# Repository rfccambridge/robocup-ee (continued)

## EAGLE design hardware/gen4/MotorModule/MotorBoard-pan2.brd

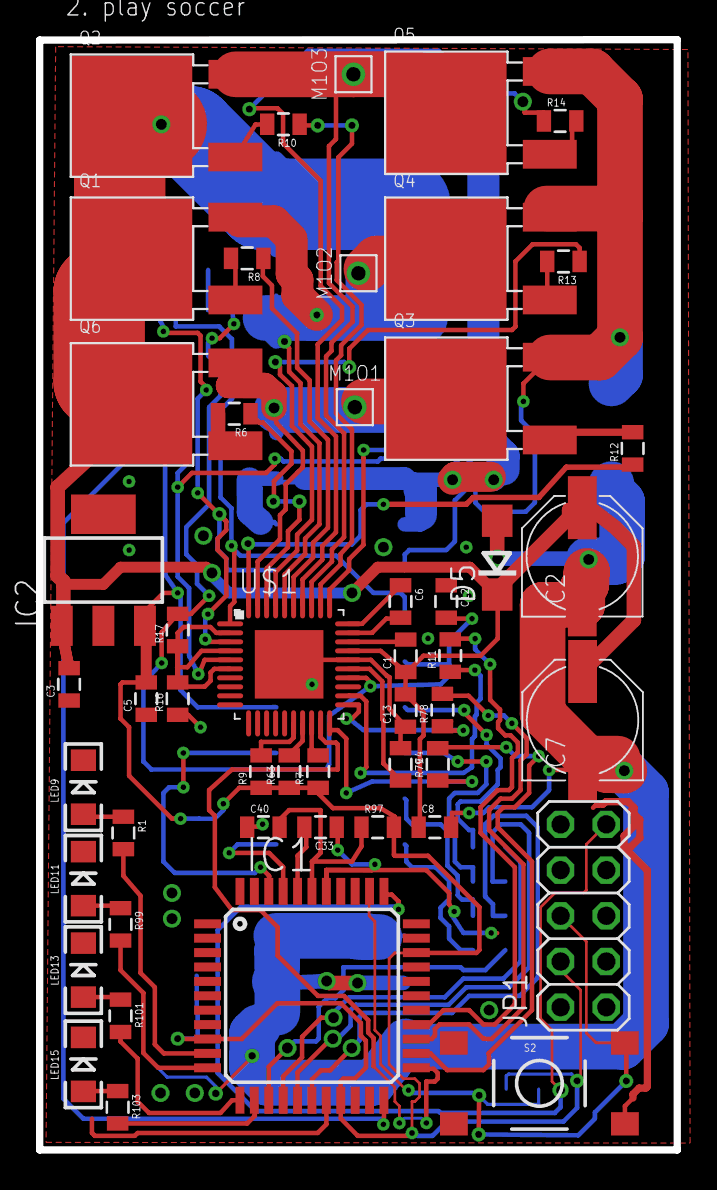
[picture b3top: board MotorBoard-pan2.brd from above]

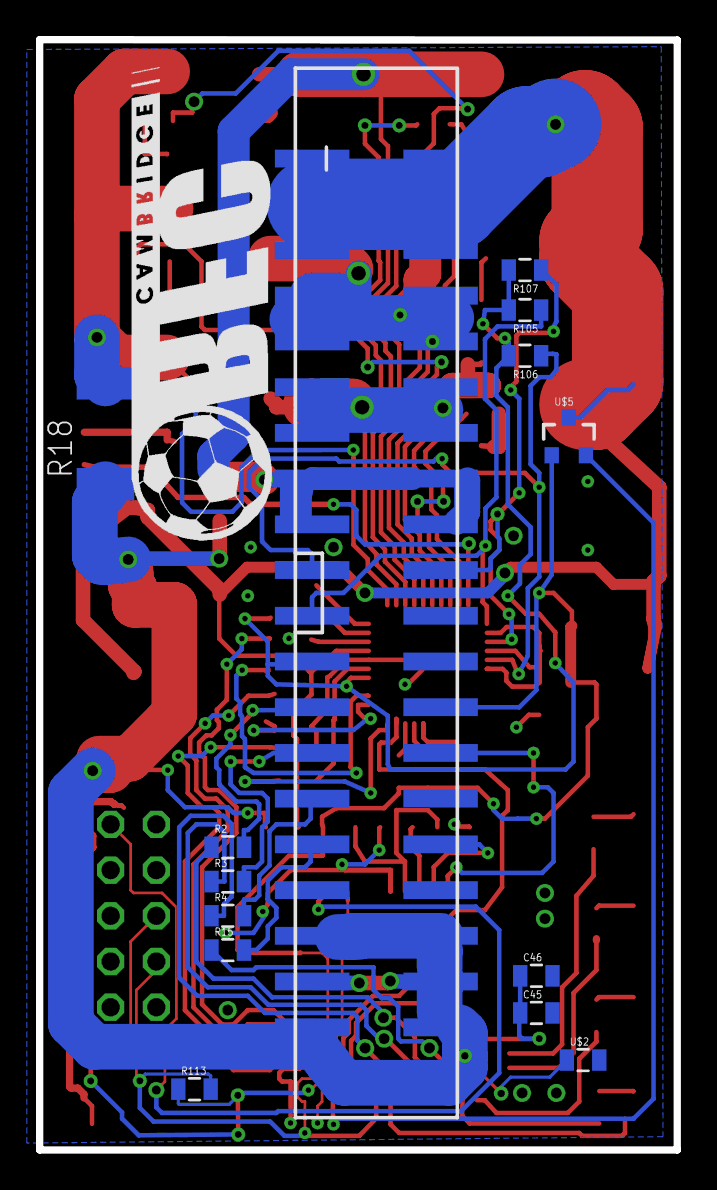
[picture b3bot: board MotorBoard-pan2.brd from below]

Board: 2 copper layers, 35.4 x 61.7 mm, 66 parts (14 on the bottom side), 62 nets.

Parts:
C1, C4, C45: 1uF; 0805
C2, C7: 100uF; PANASONIC_D
C3, C5, C8, C12, C33, C40: .1uF; 0805
C6, C13: 0.1uF; 0805
C46: .01uF; 0805
D5: DIODE-ZENERDO214AC; DO214AC
FRAME7: FRAME-LETTER; CREATIVE_COMMONS
GEN_4_REV_A: Fall 2015; LOGO
IC1: XMEGA16A4A; TQFP44
IC2: 3.3V REG; SOT223
JP1: DEBUG; 2X05
JP3: M20X2SHROUDED_SMT; 2X20_SHROUDED_SMT
LED9, LED11, LED13, LED15: LED-1206
M1O1, M1O2, M1O3: TEST_PT; TESTING_PT
Q1, Q2, Q3, Q4, Q5, Q6: DPAK
R1, R11, R78, R79, R99, R101, R103: 1k; 0805
R2, R3, R4, R15: 4.7k; 0805
R6, R8, R10, R12, R13, R14: 240; 0805
R7, R63: 30k; 0805
R9: 15k; 0805
R16, R17: 2K; 0805
R18: 0.05; R2512
R97, R105, R106, R107, R113: 10k; 0805
S2: TAC_SWITCHSMD; TACTILE-SWITCH-SMD
U$1: DRV8307; QFN40-6X6
U$2: INDUCTOR; 0805
U$5: MCP9700SMD; SOT23-3

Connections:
3.3V: C5.2, C45.1, C46.1, IC1.9, IC1.19, IC1.31, IC2.3, JP1.4, JP3.26, R7.1, R9.1, R63.1, R97.2, R113.2, U$5.1
5V: C12.2, JP3.23, R17.2, R105.2, R106.2, R107.2, U$1.24
12V: C1.1, C2.+, C3.2, C7.+, C8.1, C13.2, D5.C, IC2.1, JP3.1, JP3.2, JP3.3, JP3.4, JP3.5, JP3.6, Q1.DRAIN, Q2.DRAIN, Q6.DRAIN, U$1.27
12VGND: C2.-, C7.-, C8.2, D5.A, JP3.35, JP3.36, JP3.37, JP3.38, JP3.39, JP3.40, R18.1, U$2.1
AVCC: C40.2, IC1.39, R97.1
BREN: IC1.24, R79.2
DATA: IC1.34, JP1.9
DIR: IC1.25, R78.2
ENABLE: IC1.26, R11.2
GLED1: IC1.10, R1.2
GLED2: IC1.11, R99.2
GLED3: IC1.12, R101.2
GLED4: IC1.13, R103.2
GND: C3.1, C4.1, C5.1, C12.1, C13.1, C33.1, C40.1, C45.2, C46.2, IC1.8, IC1.18, IC1.30, IC1.38, IC2.2, IC2.4, JP1.10, JP3.22, JP3.30, JP3.33, JP3.34, LED9.C, LED11.C, LED13.C, LED15.C, R16.1, S2.4, U$1.26, U$1.P$3, U$2.2, U$5.3
M1H1: JP3.19, R106.1, U$1.5
M1H2: JP3.20, R107.1, U$1.3
M1H3: JP3.21, R105.1, U$1.1
M1O1: JP3.11, JP3.12, JP3.13, JP3.14, M1O1.P$1, Q3.DRAIN, Q6.SOURCE, U$1.39
M1O2: JP3.7, JP3.8, JP3.9, JP3.10, M1O2.P$1, Q1.SOURCE, Q4.DRAIN, U$1.36
M1O3: JP3.15, JP3.16, JP3.17, JP3.18, M1O3.P$1, Q2.SOURCE, Q5.DRAIN, U$1.33
M1QA: IC1.42, JP3.28
M1QB: IC1.41, JP3.32
MISO: IC1.16, R3.1
MOSI: IC1.15, R2.1
unnamed: LED9.A, R1.1
unnamed: C6.2, U$1.29
unnamed: JP3.27, R3.2
unnamed: JP3.29, R4.2
unnamed: Q6.GATE, R6.2
unnamed: Q1.GATE, R8.2
unnamed: C33.2, IC1.40
unnamed: C6.1, U$1.30
unnamed: Q2.GATE, R10.2
unnamed: Q3.GATE, R12.2
unnamed: C1.2, U$1.28
unnamed: Q4.GATE, R13.2
unnamed: Q5.GATE, R14.2
unnamed: C4.2, U$1.25
unnamed: R6.1, U$1.38
unnamed: R14.1, U$1.34
unnamed: R13.1, U$1.37
unnamed: R12.1, U$1.40
unnamed: R8.1, U$1.35
unnamed: R10.1, U$1.32
unnamed: R16.2, R17.1, U$1.2, U$1.4, U$1.6
unnamed: R79.1, U$1.20
unnamed: R7.2, U$1.18
unnamed: R63.2, U$1.17
unnamed: R9.2, U$1.16
unnamed: R11.1, U$1.22
unnamed: JP3.31, R15.2
unnamed: JP3.25, R2.2
unnamed: R78.1, U$1.21
unnamed: LED11.A, R99.1
unnamed: LED13.A, R101.1
unnamed: LED15.A, R103.1
O1: Q3.SOURCE, Q4.SOURCE, Q5.SOURCE, R18.2, U$1.31
PWM1: IC1.23, U$1.19
RESET: IC1.35, JP1.6, R113.1, S2.2
SCK: IC1.17, R4.1
SS_M: IC1.14, R15.1
TSENSE1: IC1.22, U$5.2

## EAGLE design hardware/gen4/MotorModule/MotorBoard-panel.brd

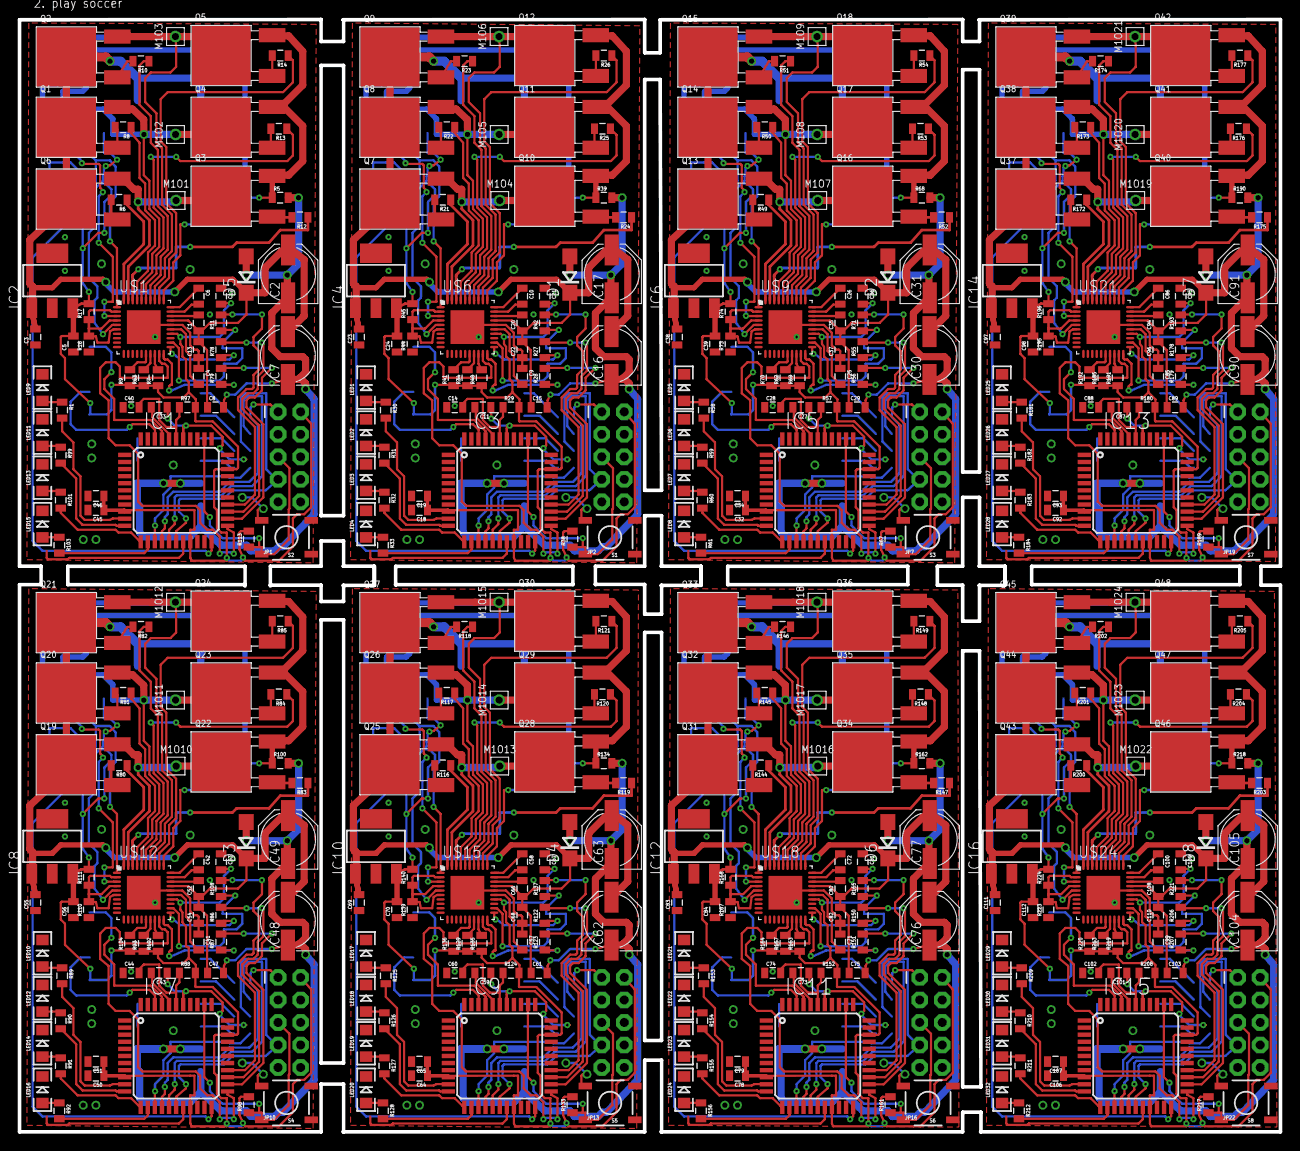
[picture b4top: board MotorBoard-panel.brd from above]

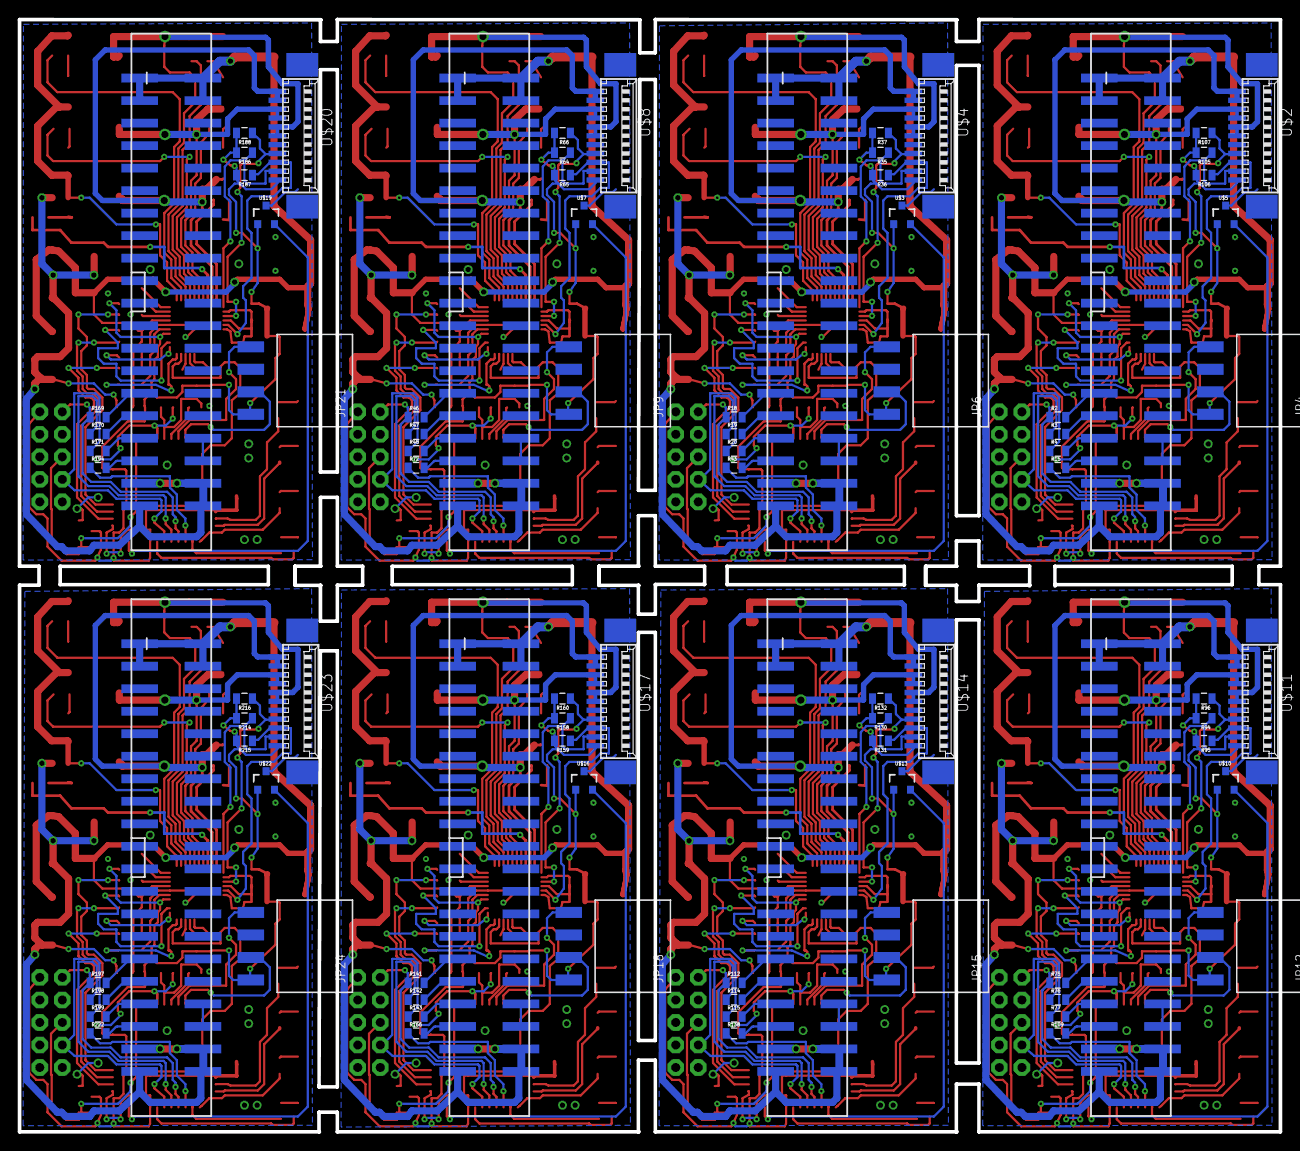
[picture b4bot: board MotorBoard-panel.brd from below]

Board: 2 copper layers, 142.3 x 125.5 mm, 522 parts (88 on the bottom side), 480 nets.

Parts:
C1, C4, C6, C9, C10, C18, C20, C25, C26, C32, C35, C41, C42, C45, C50, C52, C57, C58, C64, C66, C71, C72, C78, C80, C85, C86, C92, C94, C99, C100, C106, C108: 1uF; 0805
C2, C7, C16, C17, C30, C31, C48, C49, C62, C63, C76, C77, C90, C91, C104, C105: 100uF; PANASONIC_D
C3, C5, C8, C11, C12, C14, C15, C21, C23, C24, C27, C28, C29, C33, C36, C38, C39, C40, C43, C44, C47, C53, C55, C56, C59, C60, C61, C67, C69, C70, C73, C74, C75, C81, C83, C84, C87, C88, C89, C95, C97, C98, C101, C102, C103, C109, C111, C112: .1uF; 0805
C13, C22, C37, C54, C68, C82, C96, C110: 0.1uF; 0805
C19, C34, C46, C51, C65, C79, C93, C107: .01uF; 0805
D1, D2, D3, D4, D5, D6, D7, D8: DIODE-ZENERDO214AC; DO214AC
FRAME7: FRAME-LETTER; CREATIVE_COMMONS
GEN_4_REV_A: Fall 2015; LOGO
IC1, IC3, IC5, IC7, IC9, IC11, IC13, IC15: XMEGA16A4A; TQFP44
IC2, IC4, IC6, IC8, IC10, IC12, IC14, IC16: SOT223
JP1, JP2, JP7, JP10, JP13, JP16, JP19, JP22: 2X5-SHROUDED-NS
JP3, JP5, JP8, JP11, JP14, JP17, JP20, JP23: M20X2SHROUDED_SMT; 2X20_SHROUDED_SMT
JP4, JP6, JP9, JP12, JP15, JP18, JP21, JP24: 1X04_SMD_RA_FEMALE
LED1, LED2, LED3, LED4, LED5, LED6, LED7, LED8, LED9, LED10, LED11, LED12, LED13, LED14, LED15, LED16, LED17, LED18, LED19, LED20, LED21, LED22, LED23, LED24, LED25, LED26, LED27, LED28, LED29, LED30, LED31, LED32: LED-1206
M1O1, M1O2, M1O3, M1O4, M1O5, M1O6, M1O7, M1O8, M1O9, M1O10, M1O11, M1O12, M1O13, M1O14, M1O15, M1O16, M1O17, M1O18, M1O19, M1O20, M1O21, M1O22, M1O23, M1O24: TEST_PT; TESTING_PT
Q1, Q2, Q3, Q4, Q5, Q6, Q7, Q8, Q9, Q10, Q11, Q12, Q13, Q14, Q15, Q16, Q17, Q18, Q19, Q20, Q21, Q22, Q23, Q24, Q25, Q26, Q27, Q28, Q29, Q30, Q31, Q32, Q33, Q34, Q35, Q36, Q37, Q38, Q39, Q40, Q41, Q42, Q43, Q44, Q45, Q46, Q47, Q48: DPAK
R1, R11, R27, R28, R30, R31, R32, R33, R42, R55, R56, R58, R59, R60, R61, R71, R78, R79, R86, R87, R89, R90, R91, R92, R99, R101, R103, R108, R122, R123, R125, R126, R127, R128, R137, R150, R151, R153, R154, R155, R156, R165, R178, R179, R181, R182, R183, R184, R193, R206, R207, R209, R210, R211, R212, R221: 1k; 0805
R2, R3, R4, R15, R18, R19, R20, R43, R46, R47, R48, R72, R75, R76, R77, R109, R112, R114, R115, R138, R141, R142, R143, R166, R169, R170, R171, R194, R197, R198, R199, R222: 4.7k; 0805
R5, R39, R68, R100, R134, R162, R190, R218: 0.05; 0805
R6, R8, R10, R12, R13, R14, R21, R22, R23, R24, R25, R26, R49, R50, R51, R52, R53, R54, R80, R81, R82, R83, R84, R85, R116, R117, R118, R119, R120, R121, R144, R145, R146, R147, R148, R149, R172, R173, R174, R175, R176, R177, R200, R201, R202, R203, R204, R205: 240; 0805
R7, R34, R40, R62, R63, R69, R93, R102, R129, R135, R157, R163, R185, R191, R213, R219: 30k; 0805
R9, R41, R70, R104, R136, R164, R192, R220: 15k; 0805
R16, R17, R44, R45, R73, R74, R110, R111, R139, R140, R167, R168, R195, R196, R223, R224: 2K; 0805
R29, R35, R36, R37, R38, R57, R64, R65, R66, R67, R88, R94, R95, R96, R97, R98, R105, R106, R107, R113, R124, R130, R131, R132, R133, R152, R158, R159, R160, R161, R180, R186, R187, R188, R189, R208, R214, R215, R216, R217: 10k; 0805
S1, S2, S3, S4, S5, S6, S7, S8: TAC_SWITCHSMD; TACTILE-SWITCH-SMD
U$1, U$6, U$9, U$12, U$15, U$18, U$21, U$24: DRV8307; QFN40-6X6
U$2, U$4, U$8, U$11, U$14, U$17, U$20, U$23: MOTORCON; GEN3CON
U$3, U$5, U$7, U$10, U$13, U$16, U$19, U$22: MCP9700SMD; SOT23-3

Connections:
3.3V: C5.2, C12.2, C45.1, C46.1, IC1.9, IC1.19, IC1.31, IC2.3, JP1.2, JP4.1, R7.1, R9.1, R17.2, R63.1, R97.2, R105.2, R106.2, R107.2, R113.2, U$1.24, U$2.1, U$5.1
3.3V1: C18.1, C19.1, C21.2, C24.2, IC3.9, IC3.19, IC3.31, IC4.3, JP2.2, JP6.1, R29.2, R34.1, R35.2, R36.2, R37.2, R38.2, R40.1, R41.1, R45.2, U$3.1, U$4.1, U$6.24
3.3V2: C32.1, C34.1, C36.2, C39.2, IC5.9, IC5.19, IC5.31, IC6.3, JP7.2, JP9.1, R57.2, R62.1, R64.2, R65.2, R66.2, R67.2, R69.1, R70.1, R74.2, U$7.1, U$8.1, U$9.24
3.3V3: C50.1, C51.1, C53.2, C56.2, IC7.9, IC7.19, IC7.31, IC8.3, JP10.2, JP12.1, R88.2, R93.1, R94.2, R95.2, R96.2, R98.2, R102.1, R104.1, R111.2, U$10.1, U$11.1, U$12.24
3.3V4: C64.1, C65.1, C67.2, C70.2, IC9.9, IC9.19, IC9.31, IC10.3, JP13.2, JP15.1, R124.2, R129.1, R130.2, R131.2, R132.2, R133.2, R135.1, R136.1, R140.2, U$13.1, U$14.1, U$15.24
3.3V5: C78.1, C79.1, C81.2, C84.2, IC11.9, IC11.19, IC11.31, IC12.3, JP16.2, JP18.1, R152.2, R157.1, R158.2, R159.2, R160.2, R161.2, R163.1, R164.1, R168.2, U$16.1, U$17.1, U$18.24
3.3V6: C92.1, C93.1, C95.2, C98.2, IC13.9, IC13.19, IC13.31, IC14.3, JP19.2, JP21.1, R180.2, R185.1, R186.2, R187.2, R188.2, R189.2, R191.1, R192.1, R196.2, U$19.1, U$20.1, U$21.24
3.3V7: C106.1, C107.1, C109.2, C112.2, IC15.9, IC15.19, IC15.31, IC16.3, JP22.2, JP24.1, R208.2, R213.1, R214.2, R215.2, R216.2, R217.2, R219.1, R220.1, R224.2, U$22.1, U$23.1, U$24.24
12V: C1.1, C2.+, C3.2, C7.+, C8.1, C13.2, D5.C, IC2.1, JP3.1, JP3.2, JP3.3, JP3.4, Q1.DRAIN, Q2.DRAIN, Q6.DRAIN, U$1.27
12V1: C15.1, C16.+, C17.+, C20.1, C22.2, C23.2, D1.C, IC4.1, JP5.1, JP5.2, JP5.3, JP5.4, Q7.DRAIN, Q8.DRAIN, Q9.DRAIN, U$6.27
12V2: C29.1, C30.+, C31.+, C35.1, C37.2, C38.2, D2.C, IC6.1, JP8.1, JP8.2, JP8.3, JP8.4, Q13.DRAIN, Q14.DRAIN, Q15.DRAIN, U$9.27
12V3: C47.1, C48.+, C49.+, C52.1, C54.2, C55.2, D3.C, IC8.1, JP11.1, JP11.2, JP11.3, JP11.4, Q19.DRAIN, Q20.DRAIN, Q21.DRAIN, U$12.27
12V4: C61.1, C62.+, C63.+, C66.1, C68.2, C69.2, D4.C, IC10.1, JP14.1, JP14.2, JP14.3, JP14.4, Q25.DRAIN, Q26.DRAIN, Q27.DRAIN, U$15.27
12V5: C75.1, C76.+, C77.+, C80.1, C82.2, C83.2, D6.C, IC12.1, JP17.1, JP17.2, JP17.3, JP17.4, Q31.DRAIN, Q32.DRAIN, Q33.DRAIN, U$18.27
12V6: C89.1, C90.+, C91.+, C94.1, C96.2, C97.2, D7.C, IC14.1, JP20.1, JP20.2, JP20.3, JP20.4, Q37.DRAIN, Q38.DRAIN, Q39.DRAIN, U$21.27
12V7: C103.1, C104.+, C105.+, C108.1, C110.2, C111.2, D8.C, IC16.1, JP23.1, JP23.2, JP23.3, JP23.4, Q43.DRAIN, Q44.DRAIN, Q45.DRAIN, U$24.27
12VGND: C2.-, C7.-, C8.2, D5.A, JP3.37, JP3.38, JP3.39, JP3.40, R5.2
12VGND1: C15.2, C16.-, C17.-, D1.A, JP5.37, JP5.38, JP5.39, JP5.40, R39.2
12VGND2: C29.2, C30.-, C31.-, D2.A, JP8.37, JP8.38, JP8.39, JP8.40, R68.2
12VGND3: C47.2, C48.-, C49.-, D3.A, JP11.37, JP11.38, JP11.39, JP11.40, R100.2
12VGND4: C61.2, C62.-, C63.-, D4.A, JP14.37, JP14.38, JP14.39, JP14.40, R134.2
12VGND5: C75.2, C76.-, C77.-, D6.A, JP17.37, JP17.38, JP17.39, JP17.40, R162.2
12VGND6: C89.2, C90.-, C91.-, D7.A, JP20.37, JP20.38, JP20.39, JP20.40, R190.2
12VGND7: C103.2, C104.-, C105.-, D8.A, JP23.37, JP23.38, JP23.39, JP23.40, R218.2
AVCC: C40.2, IC1.39, R97.1
AVCC1: C14.2, IC3.39, R29.1
AVCC2: C28.2, IC5.39, R57.1
AVCC3: C44.2, IC7.39, R88.1
AVCC4: C60.2, IC9.39, R124.1
AVCC5: C74.2, IC11.39, R152.1
AVCC6: C88.2, IC13.39, R180.1
AVCC7: C102.2, IC15.39, R208.1
BREN: IC1.24, R79.2
BREN1: IC3.24, R28.2
BREN2: IC5.24, R56.2
BREN3: IC7.24, R87.2
BREN4: IC9.24, R123.2
BREN5: IC11.24, R151.2
BREN6: IC13.24, R179.2
BREN7: IC15.24, R207.2
DIR: IC1.25, R78.2
DIR1: IC3.25, R27.2
DIR2: IC5.25, R55.2
DIR3: IC7.25, R86.2
DIR4: IC9.25, R122.2
DIR5: IC11.25, R150.2
DIR6: IC13.25, R178.2
DIR7: IC15.25, R206.2
ENABLE: IC1.26, R11.2
ENABLE1: IC3.26, R42.2
ENABLE2: IC5.26, R71.2
ENABLE3: IC7.26, R108.2
ENABLE4: IC9.26, R137.2
ENABLE5: IC11.26, R165.2
ENABLE6: IC13.26, R193.2
ENABLE7: IC15.26, R221.2
GLED1: IC1.10, R1.2
GLED2: IC1.11, R99.2
GLED3: IC1.12, R101.2
GLED4: IC1.13, R103.2
GLED5: IC3.10, R30.2
GLED6: IC3.11, R31.2
GLED7: IC3.12, R32.2
GLED8: IC3.13, R33.2
GLED9: IC5.10, R58.2
GLED10: IC5.11, R59.2
GLED11: IC5.12, R60.2
GLED12: IC5.13, R61.2
GLED13: IC7.10, R89.2
GLED14: IC7.11, R90.2
GLED15: IC7.12, R91.2
GLED16: IC7.13, R92.2
GLED17: IC9.10, R125.2
GLED18: IC9.11, R126.2
GLED19: IC9.12, R127.2
GLED20: IC9.13, R128.2
GLED21: IC11.10, R153.2
GLED22: IC11.11, R154.2
GLED23: IC11.12, R155.2
GLED24: IC11.13, R156.2
GLED25: IC13.10, R181.2
GLED26: IC13.11, R182.2
GLED27: IC13.12, R183.2
GLED28: IC13.13, R184.2
GLED29: IC15.10, R209.2
GLED30: IC15.11, R210.2
GLED31: IC15.12, R211.2
GLED32: IC15.13, R212.2
GND: C3.1, C4.1, C5.1, C12.1, C13.1, C33.1, C40.1, C45.2, C46.2, IC1.8, IC1.18, IC1.30, IC1.38, IC2.2, IC2.4, JP1.4, JP1.6, JP1.8, JP1.10, JP3.34, JP3.36, JP4.3, LED9.C, LED11.C, LED13.C, LED15.C, R16.1, S2.4, U$1.26, U$1.P$3, U$2.5, U$5.3
GND1: C9.1, C11.1, C14.1, C18.2, C19.2, C21.1, C22.1, C23.1, C24.1, IC3.8, IC3.18, IC3.30, IC3.38, IC4.2, IC4.4, JP2.4, JP2.6, JP2.8, JP2.10, JP5.34, JP5.36, JP6.3, LED1.C, LED2.C, LED3.C, LED4.C, R44.1, S1.4, U$3.3, U$4.5, U$6.26, U$6.P$3
GND2: C25.1, C27.1, C28.1, C32.2, C34.2, C36.1, C37.1, C38.1, C39.1, IC5.8, IC5.18, IC5.30, IC5.38, IC6.2, IC6.4, JP7.4, JP7.6, JP7.8, JP7.10, JP8.34, JP8.36, JP9.3, LED5.C, LED6.C, LED7.C, LED8.C, R73.1, S3.4, U$7.3, U$8.5, U$9.26, U$9.P$3
GND3: C41.1, C43.1, C44.1, C50.2, C51.2, C53.1, C54.1, C55.1, C56.1, IC7.8, IC7.18, IC7.30, IC7.38, IC8.2, IC8.4, JP10.4, JP10.6, JP10.8, JP10.10, JP11.34, JP11.36, JP12.3, LED10.C, LED12.C, LED14.C, LED16.C, R110.1, S4.4, U$10.3, U$11.5, U$12.26, U$12.P$3
GND4: C57.1, C59.1, C60.1, C64.2, C65.2, C67.1, C68.1, C69.1, C70.1, IC9.8, IC9.18, IC9.30, IC9.38, IC10.2, IC10.4, JP13.4, JP13.6, JP13.8, JP13.10, JP14.34, JP14.36, JP15.3, LED17.C, LED18.C, LED19.C, LED20.C, R139.1, S5.4, U$13.3, U$14.5, U$15.26, U$15.P$3
GND5: C71.1, C73.1, C74.1, C78.2, C79.2, C81.1, C82.1, C83.1, C84.1, IC11.8, IC11.18, IC11.30, IC11.38, IC12.2, IC12.4, JP16.4, JP16.6, JP16.8, JP16.10, JP17.34, JP17.36, JP18.3, LED21.C, LED22.C, LED23.C, LED24.C, R167.1, S6.4, U$16.3, U$17.5, U$18.26, U$18.P$3
GND6: C85.1, C87.1, C88.1, C92.2, C93.2, C95.1, C96.1, C97.1, C98.1, IC13.8, IC13.18, IC13.30, IC13.38, IC14.2, IC14.4, JP19.4, JP19.6, JP19.8, JP19.10, JP20.34, JP20.36, JP21.3, LED25.C, LED26.C, LED27.C, LED28.C, R195.1, S7.4, U$19.3, U$20.5, U$21.26, U$21.P$3
GND7: C99.1, C101.1, C102.1, C106.2, C107.2, C109.1, C110.1, C111.1, C112.1, IC15.8, IC15.18, IC15.30, IC15.38, IC16.2, IC16.4, JP22.4, JP22.6, JP22.8, JP22.10, JP23.34, JP23.36, JP24.3, LED29.C, LED30.C, LED31.C, LED32.C, R223.1, S8.4, U$22.3, U$23.5, U$24.26, U$24.P$3
M1H1: R106.1, U$1.5, U$2.3
M1H2: R107.1, U$1.3, U$2.4
M1H3: R105.1, U$1.1, U$2.2
M1H4: R35.1, U$4.2, U$6.1
M1H5: R37.1, U$4.4, U$6.3
M1H6: R36.1, U$4.3, U$6.5
M1H7: R64.1, U$8.2, U$9.1
M1H8: R66.1, U$8.4, U$9.3
M1H9: R65.1, U$8.3, U$9.5
M1H10: R94.1, U$11.2, U$12.1
M1H11: R96.1, U$11.4, U$12.3
M1H12: R95.1, U$11.3, U$12.5
M1H13: R130.1, U$14.2, U$15.1
M1H14: R132.1, U$14.4, U$15.3
M1H15: R131.1, U$14.3, U$15.5
M1H16: R158.1, U$17.2, U$18.1
M1H17: R160.1, U$17.4, U$18.3
M1H18: R159.1, U$17.3, U$18.5
M1H19: R186.1, U$20.2, U$21.1
M1H20: R188.1, U$20.4, U$21.3
M1H21: R187.1, U$20.3, U$21.5
M1H22: R214.1, U$23.2, U$24.1
M1H23: R216.1, U$23.4, U$24.3
M1H24: R215.1, U$23.3, U$24.5
M1O1: M1O1.P$1, Q3.DRAIN, Q6.SOURCE, U$1.39, U$2.10, U$2.11
M1O2: M1O2.P$1, Q1.SOURCE, Q4.DRAIN, U$1.36, U$2.8, U$2.9
M1O3: M1O3.P$1, Q2.SOURCE, Q5.DRAIN, U$1.33, U$2.6, U$2.7
M1O4: M1O4.P$1, Q7.SOURCE, Q10.DRAIN, U$4.10, U$4.11, U$6.39
M1O5: M1O5.P$1, Q8.SOURCE, Q11.DRAIN, U$4.8, U$4.9, U$6.36
M1O6: M1O6.P$1, Q9.SOURCE, Q12.DRAIN, U$4.6, U$4.7, U$6.33
M1O7: M1O7.P$1, Q13.SOURCE, Q16.DRAIN, U$8.10, U$8.11, U$9.39
M1O8: M1O8.P$1, Q14.SOURCE, Q17.DRAIN, U$8.8, U$8.9, U$9.36
M1O9: M1O9.P$1, Q15.SOURCE, Q18.DRAIN, U$8.6, U$8.7, U$9.33
M1O10: M1O10.P$1, Q19.SOURCE, Q22.DRAIN, U$11.10, U$11.11, U$12.39
M1O11: M1O11.P$1, Q20.SOURCE, Q23.DRAIN, U$11.8, U$11.9, U$12.36
M1O12: M1O12.P$1, Q21.SOURCE, Q24.DRAIN, U$11.6, U$11.7, U$12.33
M1O13: M1O13.P$1, Q25.SOURCE, Q28.DRAIN, U$14.10, U$14.11, U$15.39
M1O14: M1O14.P$1, Q26.SOURCE, Q29.DRAIN, U$14.8, U$14.9, U$15.36
M1O15: M1O15.P$1, Q27.SOURCE, Q30.DRAIN, U$14.6, U$14.7, U$15.33
M1O16: M1O16.P$1, Q31.SOURCE, Q34.DRAIN, U$17.10, U$17.11, U$18.39
M1O17: M1O17.P$1, Q32.SOURCE, Q35.DRAIN, U$17.8, U$17.9, U$18.36
M1O18: M1O18.P$1, Q33.SOURCE, Q36.DRAIN, U$17.6, U$17.7, U$18.33
M1O19: M1O19.P$1, Q37.SOURCE, Q40.DRAIN, U$20.10, U$20.11, U$21.39
M1O20: M1O20.P$1, Q38.SOURCE, Q41.DRAIN, U$20.8, U$20.9, U$21.36
M1O21: M1O21.P$1, Q39.SOURCE, Q42.DRAIN, U$20.6, U$20.7, U$21.33
M1O22: M1O22.P$1, Q43.SOURCE, Q46.DRAIN, U$23.10, U$23.11, U$24.39
M1O23: M1O23.P$1, Q44.SOURCE, Q47.DRAIN, U$23.8, U$23.9, U$24.36
M1O24: M1O24.P$1, Q45.SOURCE, Q48.DRAIN, U$23.6, U$23.7, U$24.33
M1QA: IC1.42, JP4.2
M1QA1: IC3.42, JP6.2
M1QA2: IC5.42, JP9.2
M1QA3: IC7.42, JP12.2
M1QA4: IC9.42, JP15.2
M1QA5: IC11.42, JP18.2
M1QA6: IC13.42, JP21.2
M1QA7: IC15.42, JP24.2
M1QB: IC1.41, JP4.4
M1QB1: IC3.41, JP6.4
M1QB2: IC5.41, JP9.4
M1QB3: IC7.41, JP12.4
M1QB4: IC9.41, JP15.4
M1QB5: IC11.41, JP18.4
M1QB6: IC13.41, JP21.4
M1QB7: IC15.41, JP24.4
MISO: IC1.16, R3.1
MISO1: IC3.16, R19.1
MISO2: IC5.16, R47.1
MISO3: IC7.16, R76.1
MISO4: IC9.16, R114.1
MISO5: IC11.16, R142.1
MISO6: IC13.16, R170.1
MISO7: IC15.16, R198.1
MOSI: IC1.15, JP1.1, R2.1
MOSI1: IC3.15, JP2.1, R18.1
MOSI2: IC5.15, JP7.1, R46.1
MOSI3: IC7.15, JP10.1, R75.1
MOSI4: IC9.15, JP13.1, R112.1
MOSI5: IC11.15, JP16.1, R141.1
MOSI6: IC13.15, JP19.1, R169.1
MOSI7: IC15.15, JP22.1, R197.1
unnamed: LED9.A, R1.1
unnamed: C6.2, U$1.29
unnamed: JP3.31, R3.2
unnamed: JP3.33, R4.2
unnamed: JP5.31, R19.2
unnamed: Q6.GATE, R6.2
unnamed: Q1.GATE, R8.2
unnamed: C33.2, IC1.40
unnamed: C6.1, U$1.30
unnamed: Q2.GATE, R10.2
unnamed: Q3.GATE, R12.2
unnamed: C1.2, U$1.28
unnamed: Q4.GATE, R13.2
unnamed: Q5.GATE, R14.2
unnamed: C4.2, U$1.25
unnamed: R6.1, U$1.40
unnamed: R14.1, U$1.32
unnamed: R13.1, U$1.35
unnamed: R12.1, U$1.38
unnamed: R8.1, U$1.37
unnamed: R10.1, U$1.34
unnamed: R16.2, R17.1, U$1.2, U$1.4, U$1.6
unnamed: R79.1, U$1.20
unnamed: R7.2, U$1.18
unnamed: JP5.33, R20.2
unnamed: Q7.GATE, R21.2
unnamed: R63.2, U$1.17
unnamed: Q8.GATE, R22.2
unnamed: R9.2, U$1.16
unnamed: R11.1, U$1.22
unnamed: Q9.GATE, R23.2
unnamed: JP3.35, R15.2
unnamed: Q10.GATE, R24.2
unnamed: Q11.GATE, R25.2
unnamed: Q12.GATE, R26.2
unnamed: R21.1, U$6.40
unnamed: R26.1, U$6.32
unnamed: R25.1, U$6.35
unnamed: R24.1, U$6.38
unnamed: R22.1, U$6.37
unnamed: JP3.29, R2.2
unnamed: R23.1, U$6.34
unnamed: R27.1, U$6.21
unnamed: LED1.A, R30.1
unnamed: LED2.A, R31.1
unnamed: LED3.A, R32.1
unnamed: LED4.A, R33.1
unnamed: JP5.29, R18.2
unnamed: C11.2, IC3.40
unnamed: C10.1, U$6.30
unnamed: C20.2, U$6.28
unnamed: C9.2, U$6.25
unnamed: R28.1, U$6.20
unnamed: R40.2, U$6.18
unnamed: R34.2, U$6.17
unnamed: R41.2, U$6.16
unnamed: R42.1, U$6.22
unnamed: JP5.35, R43.2
unnamed: R44.2, R45.1, U$6.2, U$6.4, U$6.6
unnamed: C10.2, U$6.29
unnamed: JP8.31, R47.2
unnamed: JP8.33, R48.2
unnamed: Q13.GATE, R49.2
unnamed: Q14.GATE, R50.2
unnamed: Q15.GATE, R51.2
unnamed: Q16.GATE, R52.2
unnamed: Q17.GATE, R53.2
unnamed: Q18.GATE, R54.2
unnamed: R49.1, U$9.40
unnamed: R54.1, U$9.32
unnamed: R53.1, U$9.35
unnamed: R52.1, U$9.38
unnamed: R50.1, U$9.37
unnamed: R51.1, U$9.34
unnamed: R55.1, U$9.21
unnamed: LED5.A, R58.1
unnamed: LED6.A, R59.1
unnamed: LED7.A, R60.1
unnamed: LED8.A, R61.1
unnamed: JP8.29, R46.2
unnamed: C27.2, IC5.40
unnamed: C26.1, U$9.30
unnamed: C35.2, U$9.28
unnamed: C25.2, U$9.25
unnamed: R56.1, U$9.20
unnamed: R69.2, U$9.18
unnamed: R62.2, U$9.17
unnamed: R70.2, U$9.16
unnamed: R71.1, U$9.22
unnamed: JP8.35, R72.2
unnamed: R73.2, R74.1, U$9.2, U$9.4, U$9.6
unnamed: C26.2, U$9.29
unnamed: JP11.31, R76.2
unnamed: R78.1, U$1.21
unnamed: JP11.33, R77.2
unnamed: Q19.GATE, R80.2
unnamed: Q20.GATE, R81.2
unnamed: Q21.GATE, R82.2
unnamed: Q22.GATE, R83.2
unnamed: Q23.GATE, R84.2
unnamed: Q24.GATE, R85.2
unnamed: R80.1, U$12.40
unnamed: R85.1, U$12.32
unnamed: R84.1, U$12.35
unnamed: R83.1, U$12.38
unnamed: R81.1, U$12.37
unnamed: R82.1, U$12.34
unnamed: R86.1, U$12.21
unnamed: LED11.A, R99.1
unnamed: LED10.A, R89.1
unnamed: LED12.A, R90.1
unnamed: LED13.A, R101.1
unnamed: LED14.A, R91.1
unnamed: LED15.A, R103.1
unnamed: LED16.A, R92.1
unnamed: JP11.29, R75.2
unnamed: C43.2, IC7.40
unnamed: C42.1, U$12.30
unnamed: C52.2, U$12.28
unnamed: C41.2, U$12.25
unnamed: R87.1, U$12.20
unnamed: R102.2, U$12.18
unnamed: R93.2, U$12.17
unnamed: R104.2, U$12.16
unnamed: R108.1, U$12.22
unnamed: JP11.35, R109.2
unnamed: R110.2, R111.1, U$12.2, U$12.4, U$12.6
unnamed: C42.2, U$12.29
unnamed: JP14.31, R114.2
unnamed: JP14.33, R115.2
unnamed: Q25.GATE, R116.2
unnamed: Q26.GATE, R117.2
unnamed: Q27.GATE, R118.2
unnamed: Q28.GATE, R119.2
unnamed: Q29.GATE, R120.2
unnamed: Q30.GATE, R121.2
unnamed: R116.1, U$15.40
unnamed: R121.1, U$15.32
unnamed: R120.1, U$15.35
unnamed: R119.1, U$15.38
unnamed: R117.1, U$15.37
unnamed: R118.1, U$15.34
unnamed: R122.1, U$15.21
unnamed: LED17.A, R125.1
unnamed: LED18.A, R126.1
unnamed: LED19.A, R127.1
unnamed: LED20.A, R128.1
unnamed: JP14.29, R112.2
unnamed: C59.2, IC9.40
unnamed: C58.1, U$15.30
unnamed: C66.2, U$15.28
unnamed: C57.2, U$15.25
unnamed: R123.1, U$15.20
unnamed: R135.2, U$15.18
unnamed: R129.2, U$15.17
unnamed: R136.2, U$15.16
unnamed: R137.1, U$15.22
unnamed: JP14.35, R138.2
unnamed: R139.2, R140.1, U$15.2, U$15.4, U$15.6
unnamed: C58.2, U$15.29
unnamed: JP17.31, R142.2
unnamed: JP17.33, R143.2
unnamed: Q31.GATE, R144.2
unnamed: Q32.GATE, R145.2
unnamed: Q33.GATE, R146.2
unnamed: Q34.GATE, R147.2
unnamed: Q35.GATE, R148.2
unnamed: Q36.GATE, R149.2
unnamed: R144.1, U$18.40
unnamed: R149.1, U$18.32
unnamed: R148.1, U$18.35
unnamed: R147.1, U$18.38
unnamed: R145.1, U$18.37
unnamed: R146.1, U$18.34
unnamed: R150.1, U$18.21
unnamed: LED21.A, R153.1
unnamed: LED22.A, R154.1
unnamed: LED23.A, R155.1
unnamed: LED24.A, R156.1
unnamed: JP17.29, R141.2
unnamed: C73.2, IC11.40
unnamed: C72.1, U$18.30
unnamed: C80.2, U$18.28
unnamed: C71.2, U$18.25
unnamed: R151.1, U$18.20
unnamed: R163.2, U$18.18
unnamed: R157.2, U$18.17
unnamed: R164.2, U$18.16
unnamed: R165.1, U$18.22
unnamed: JP17.35, R166.2
unnamed: R167.2, R168.1, U$18.2, U$18.4, U$18.6
unnamed: C72.2, U$18.29
unnamed: JP20.31, R170.2
unnamed: JP20.33, R171.2
unnamed: Q37.GATE, R172.2
unnamed: Q38.GATE, R173.2
unnamed: Q39.GATE, R174.2
unnamed: Q40.GATE, R175.2
unnamed: Q41.GATE, R176.2
unnamed: Q42.GATE, R177.2
unnamed: R172.1, U$21.40
unnamed: R177.1, U$21.32
unnamed: R176.1, U$21.35
unnamed: R175.1, U$21.38
unnamed: R173.1, U$21.37
unnamed: R174.1, U$21.34
unnamed: R178.1, U$21.21
unnamed: LED25.A, R181.1
unnamed: LED26.A, R182.1
unnamed: LED27.A, R183.1
unnamed: LED28.A, R184.1
unnamed: JP20.29, R169.2
unnamed: C87.2, IC13.40
unnamed: C86.1, U$21.30
unnamed: C94.2, U$21.28
unnamed: C85.2, U$21.25
unnamed: R179.1, U$21.20
unnamed: R191.2, U$21.18
unnamed: R185.2, U$21.17
unnamed: R192.2, U$21.16
unnamed: R193.1, U$21.22
unnamed: JP20.35, R194.2
unnamed: R195.2, R196.1, U$21.2, U$21.4, U$21.6
unnamed: C86.2, U$21.29
unnamed: JP23.31, R198.2
unnamed: JP23.33, R199.2
unnamed: Q43.GATE, R200.2
unnamed: Q44.GATE, R201.2
unnamed: Q45.GATE, R202.2
unnamed: Q46.GATE, R203.2
unnamed: Q47.GATE, R204.2
unnamed: Q48.GATE, R205.2
unnamed: R200.1, U$24.40
unnamed: R205.1, U$24.32
unnamed: R204.1, U$24.35
unnamed: R203.1, U$24.38
unnamed: R201.1, U$24.37
unnamed: R202.1, U$24.34
unnamed: R206.1, U$24.21
unnamed: LED29.A, R209.1
unnamed: LED30.A, R210.1
unnamed: LED31.A, R211.1
unnamed: LED32.A, R212.1
unnamed: JP23.29, R197.2
unnamed: C101.2, IC15.40
unnamed: C100.1, U$24.30
unnamed: C108.2, U$24.28
unnamed: C99.2, U$24.25
unnamed: R207.1, U$24.20
unnamed: R219.2, U$24.18
unnamed: R213.2, U$24.17
unnamed: R220.2, U$24.16
unnamed: R221.1, U$24.22
unnamed: JP23.35, R222.2
unnamed: R223.2, R224.1, U$24.2, U$24.4, U$24.6
unnamed: C100.2, U$24.29
O1: Q3.SOURCE, Q4.SOURCE, Q5.SOURCE, R5.1, U$1.31
O2: Q10.SOURCE, Q11.SOURCE, Q12.SOURCE, R39.1, U$6.31
O3: Q16.SOURCE, Q17.SOURCE, Q18.SOURCE, R68.1, U$9.31
O4: Q22.SOURCE, Q23.SOURCE, Q24.SOURCE, R100.1, U$12.31
O5: Q28.SOURCE, Q29.SOURCE, Q30.SOURCE, R134.1, U$15.31
O6: Q34.SOURCE, Q35.SOURCE, Q36.SOURCE, R162.1, U$18.31
O7: Q40.SOURCE, Q41.SOURCE, Q42.SOURCE, R190.1, U$21.31
O8: Q46.SOURCE, Q47.SOURCE, Q48.SOURCE, R218.1, U$24.31
PWM1: IC1.23, U$1.19
PWM2: IC3.23, U$6.19
PWM3: IC5.23, U$9.19
PWM4: IC7.23, U$12.19
PWM5: IC9.23, U$15.19
PWM6: IC11.23, U$18.19
PWM7: IC13.23, U$21.19
PWM8: IC15.23, U$24.19
RESET: IC1.35, JP1.5, R113.1, S2.2
RESET1: IC3.35, JP2.5, R38.1, S1.2
RESET2: IC5.35, JP7.5, R67.1, S3.2
RESET3: IC7.35, JP10.5, R98.1, S4.2
RESET4: IC9.35, JP13.5, R133.1, S5.2
RESET5: IC11.35, JP16.5, R161.1, S6.2
RESET6: IC13.35, JP19.5, R189.1, S7.2
RESET7: IC15.35, JP22.5, R217.1, S8.2
SCK: IC1.17, JP1.7, R4.1
SCK1: IC3.17, JP2.7, R20.1
SCK2: IC5.17, JP7.7, R48.1
SCK3: IC7.17, JP10.7, R77.1
SCK4: IC9.17, JP13.7, R115.1
SCK5: IC11.17, JP16.7, R143.1
SCK6: IC13.17, JP19.7, R171.1
SCK7: IC15.17, JP22.7, R199.1
SS_M: IC1.14, R15.1
SS_M1: IC3.14, R43.1
SS_M2: IC5.14, R72.1
SS_M3: IC7.14, R109.1
SS_M4: IC9.14, R138.1
SS_M5: IC11.14, R166.1
SS_M6: IC13.14, R194.1
SS_M7: IC15.14, R222.1
TSENSE1: IC1.22, U$5.2
TSENSE2: IC3.22, U$3.2
TSENSE3: IC5.22, U$7.2
TSENSE4: IC7.22, U$10.2
TSENSE5: IC9.22, U$13.2
TSENSE6: IC11.22, U$16.2
TSENSE7: IC13.22, U$19.2
TSENSE8: IC15.22, U$22.2

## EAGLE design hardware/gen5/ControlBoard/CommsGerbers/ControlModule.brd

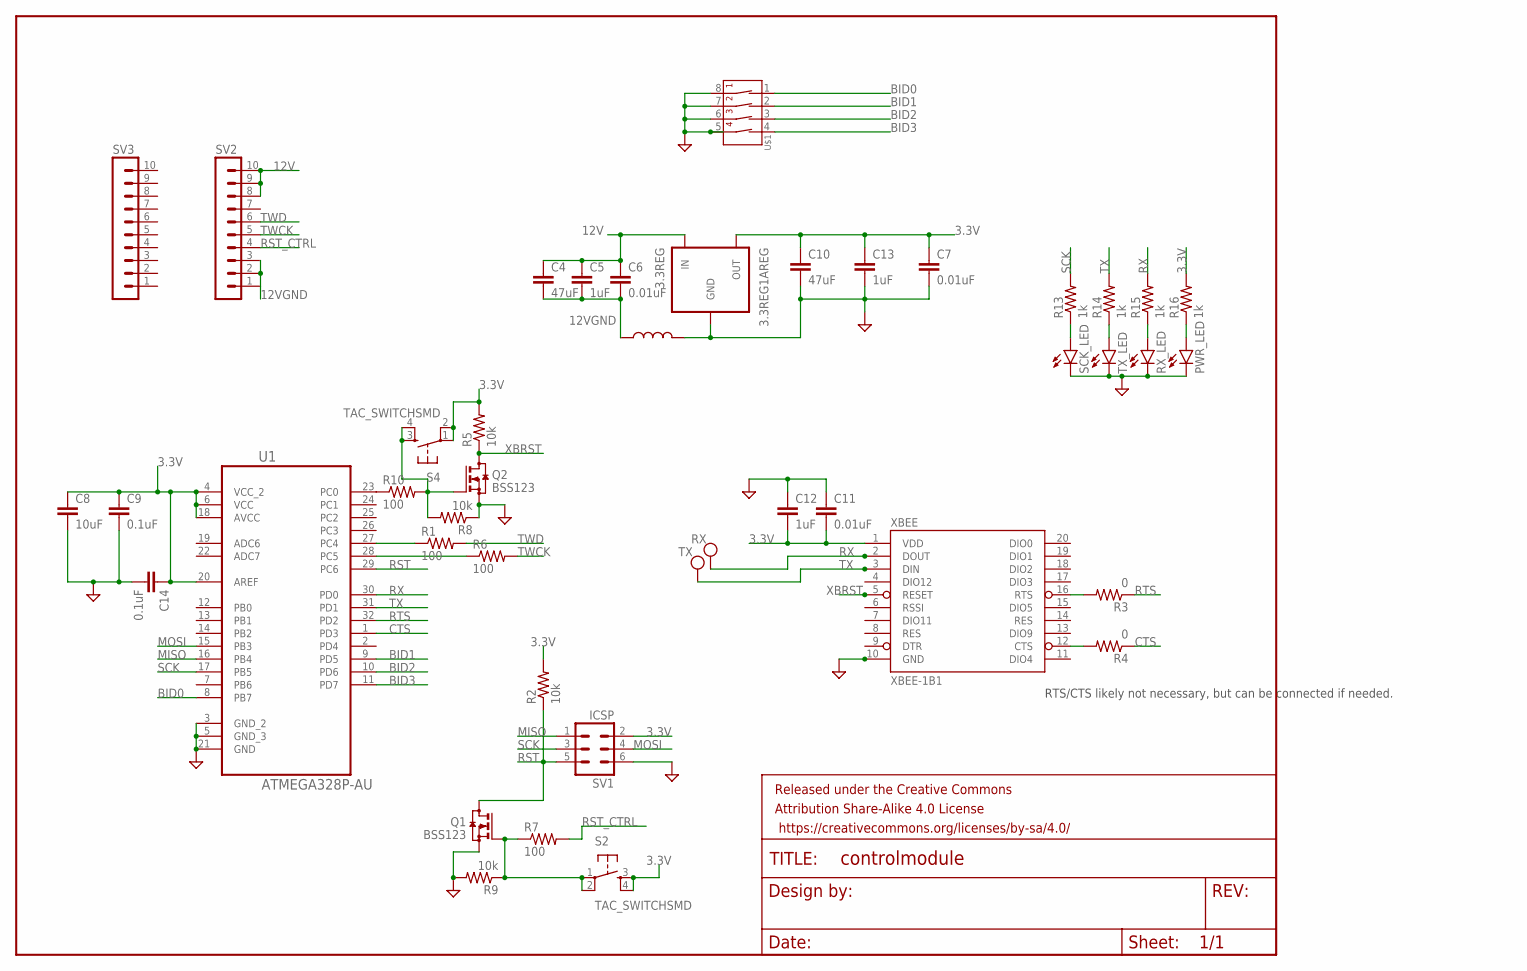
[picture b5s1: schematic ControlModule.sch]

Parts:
3.3REG: 3.3REG1AREG; DPAK
C4, C10: 47uF; 1206
C5, C12, C13: 1uF; 0805
C6, C7, C11: 0.01uF; 0805
C8: 10uF; 0805
C9, C14: 0.1uF; 0805
FRAME1: FRAME-LETTER; CREATIVE_COMMONS
PWR_LED: LED1206; LED-1206
Q1, Q2: BSS123; SOT23
R1, R6, R7, R10: 100; 0805
R2, R5, R8, R9: 10k; 0805
R3, R4: 0; 0805
R13, R14, R15, R16: 1k; 0805
RX: TEST_PT; TESTING_PT
RX_LED: LED1206; LED-1206
S2, S4: TAC_SWITCHSMD; TACTILE-SWITCH-SMD
SCK_LED: LED1206; LED-1206
SV1: ICSP; MA03-2
SV2, SV3: MA10-1W
TX: TEST_PT; TESTING_PT
TX_LED: LED1206; LED-1206
U1: ATMEGA328P-AU; QFP80P900X900X120-32N
U$1: 4-POS-DIP; 4-POS-DIP-SMD
U$2: INDUCTOR; 0805
XBEE: XBEE-1B1; XBEE-1

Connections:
3.3V: 3.3REG.SOURCE (OUT), C7.1, C8.1, C9.1, C10.1, C11.2, C12.2, C13.1, C14.1, R2.2, R5.2, R16.2, S2.3, S2.4, S4.1, S4.2, SV1.2, U1.4 (VCC_2), U1.6 (VCC), U1.18 (AVCC), U1.20 (AREF), XBEE.1 (VDD)
12V: 3.3REG.GATE (IN), C4.1, C5.1, C6.1, SV2.8, SV2.9, SV2.10
12VGND: C4.2, C5.2, C6.2, SV2.1, SV2.2, SV2.3, U$2.1
BID0: U1.8 (PB7), U$1.1 (1A)
BID1: U1.9 (PD5), U$1.2 (2A)
BID2: U1.10 (PD6), U$1.3 (3A)
BID3: U1.11 (PD7), U$1.4 (4A)
CTS: R4.1, U1.1 (PD3)
GND: 3.3REG.DRAIN (GND), C7.2, C8.2, C9.2, C10.2, C11.1, C12.1, C13.2, C14.2, PWR_LED.C, Q1.2 (S), Q2.2 (S), R8.1, R9.2, RX_LED.C, SCK_LED.C, SV1.6, TX_LED.C, U1.3 (GND_2), U1.5 (GND_3), U1.21 (GND), U$1.5 (4B), U$1.6 (3B), U$1.7 (2B), U$1.8 (1B), U$2.2, XBEE.10 (GND)
MISO: SV1.1, U1.16 (PB4)
MOSI: SV1.4, U1.15 (PB3)
unnamed: R3.2, XBEE.16 (RTS)
unnamed: R13.1, SCK_LED.A
unnamed: R4.2, XBEE.12 (CTS)
unnamed: R1.1, U1.27 (PC4)
unnamed: R10.1, U1.23 (PC0)
unnamed: R6.1, U1.28 (PC5)
unnamed: R14.1, TX_LED.A
unnamed: R15.1, RX_LED.A
unnamed: PWR_LED.A, R16.1
unnamed: Q2.1 (G), R8.2, R10.2, S4.3, S4.4
unnamed: Q1.1 (G), R7.1, R9.1, S2.1, S2.2
RST: Q1.3 (D), R2.1, SV1.5, U1.29 (PC6)
RST_CTRL: R7.2, SV2.4
RTS: R3.1, U1.32 (PD2)
RX: R15.2, RX.P$1, U1.30 (PD0), XBEE.2 (DOUT)
SCK: R13.2, SV1.3, U1.17 (PB5)
TWCK: R6.2, SV2.5
TWD: R1.2, SV2.6
TX: R14.2, TX.P$1, U1.31 (PD1), XBEE.3 (DIN)
XBRST: Q2.3 (D), R5.1, XBEE.5 (RESET)

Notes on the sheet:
RTS/CTS likely not necessary, but can be connected if needed.
